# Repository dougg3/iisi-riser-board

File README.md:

# Macintosh IIsi power supply riser board replica

This is a replica of the daughterboard found in the Apple/Sony Macintosh IIsi APS-06 power supply. The part number printed on the original board is AP41S. This PCB often suffers from severe corrosion damage due to electrolytic capacitor leakage, so this project aims to provide you with a way to replace it with a brand new PCB.

To aid with reverse engineering, all of the components were removed from the board and inspected out of circuit. I used pictures of the bare board ([top](barepcb_top.jpg?raw=true), [bottom](barepcb_bottom.jpg?raw=true)) to draw a replica design. The [Bomarc schematics](https://www.macdat.net/files/pdf/apple/schematics/bomarc/mac_iisi.pdf) were a huge help with part identification and understanding the circuit. However, those schematics did have a few mistakes, which I have corrected in my schematics and BOM. My replica design has been successfully used to build a brand new board with all new components except for the two obsolete ICs.

## Schematics

[Here is a link to the schematics in PDF format](iisi-riser-board.pdf?raw=true).

## Build Notes

[Here is an image that shows the names that I arbitrarily gave each component, along with their values](placement.png?raw=true). It may help if you decide to build one yourself.

The trimpot is used to adjust the voltage. If you build one yourself, it may be prudent to test the power supply with a dummy load connected and get the trimpot adjusted properly before trying to use it in an actual Mac IIsi.

## BOM

[Here is the bill of materials in CSV format](iisi-riser-board.csv). All of the parts with the exception of the two obsolete Mitsubishi/Renesas ICs can be purchased brand new from Digi-Key. Note that you need to purchase ten of the leadframe pins for the edge connector.

## Gerbers

[Here is a link to the gerbers](gerbers/) if you want to have boards made yourself. I ordered them as 30.5x36mm, single layer, 0.8 mm thickness, HASL, and solder mask and silkscreen only on one side.

## Purchasing

For convenience, I plan on building some of these up for sale to recoup my costs on this project. I also will save some bare PCBs you can purchase if you just want to move all of your components over from your original corrosion-damaged PCB. Stay tuned for more info on how I will sell these.

## KiCad Design Notes

- The trace widths were very strange on this board, so I just used polygon copper fills to redraw them all. I also manually tweaked each pad's size to bring everything close to the original design.
- The board fails some DRC checks which I have added as exclusions.
- The three GND-to-GND 0-ohm resistors cause three "Unconnected Items" warnings in the DRC. These can be safely ignored.

## Differences from Bomarc reverse-engineered schematics

- The resistor labeled as 8200 ohms in Bomarc's schematic is really 8.2 ohms.
- The chip marked as `44` is really a Mitsubishi/Renesas M51944BML, not a transistor. It's a voltage detector/reset IC.
- The diode marked as `=B` is a Schottky diode; I opted to use the onsemi SB05-05C, which is also marked as `B`.
- I have identified all of the ceramic capacitor values using an LCR meter.
- Pin 9 of the edge connector has been correctly labeled as GND.

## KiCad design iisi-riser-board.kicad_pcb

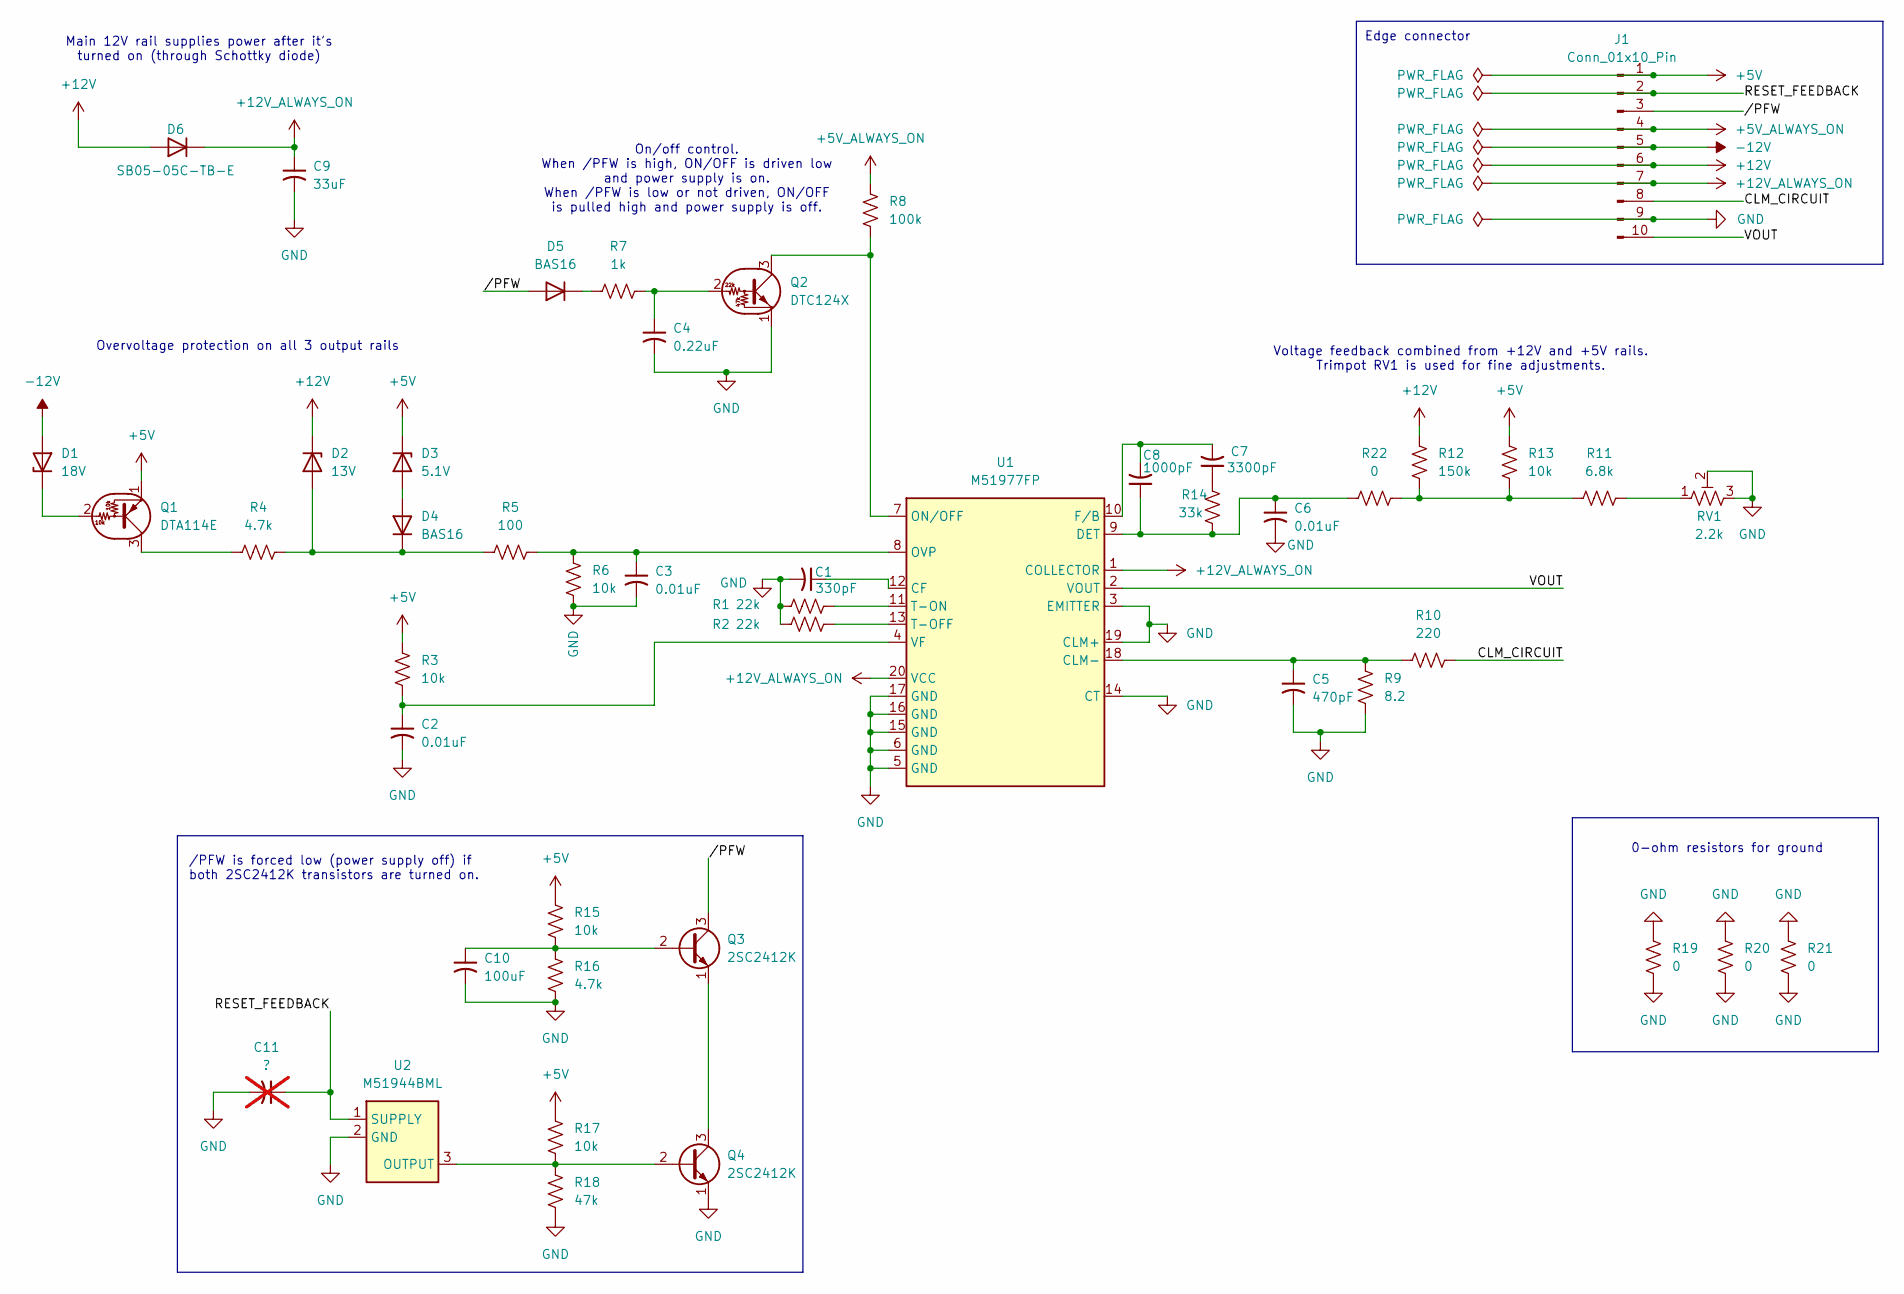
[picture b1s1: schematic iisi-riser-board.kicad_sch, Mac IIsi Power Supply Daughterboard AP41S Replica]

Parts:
C1: 330pF; C_0805_2012Metric; Digi-Key Part 399-C0805C331J5GACTUCT-ND
C2, C3, C6: 0.01uF; C_0805_2012Metric; Digi-Key Part 399-C0805C103K5RACTUCT-ND
C4: 0.22uF; C_1206_3216Metric; Digi-Key Part 445-2283-1-ND
C5: 470pF; C_0805_2012Metric; Digi-Key Part 311-1119-1-ND
C7: 3300pF; C_0805_2012Metric; Digi-Key Part 399-C0805C332J5GACTUCT-ND
C8: 1000pF; C_0805_2012Metric; Digi-Key Part 399-C0805C102J5GACTUCT-ND
C9: 33uF; CP_Elec; Digi-Key Part 565-4768-1-ND
C10: 100uF; CP_Elec; Digi-Key Part 493-3967-1-ND
C11: ?; C_0805_2012Metric; not fitted
D1: 18V; SC-59-Diode; Digi-Key Part MMBZ5248B-FDICT-ND
D2: 13V; SC-59-Diode; Digi-Key Part BZX84C13-FDICT-ND
D3: 5.1V; SC-59-Diode; Digi-Key Part SZBZX84C5V1LT3GOSCT-ND
D4, D5: BAS16; SC-59-Diode; Digi-Key Part 1727-2887-1-ND
D6: SB05-05C-TB-E; SC-59-Diode; Digi-Key Part SB05-05C-TB-EOSCT-ND
J1: Conn_01x10_Pin; EdgeConnector10; Digi-Key Part A122175CT-ND
Q1: DTA114E; SOT-346-Rohm; Digi-Key Part DTA114EKAT146CT-ND
Q2: DTC124X; SOT-346-Rohm; Digi-Key Part DTC124XKAT146CT-ND
Q3, Q4: 2SC2412K; SOT-346-Rohm; Digi-Key Part 2SC2412KT146RCT-ND
R1, R2: 22k; R_0805_2012Metric; Digi-Key Part A129765CT-ND
R3, R6, R13, R15, R17: 10k; R_0805_2012Metric; Digi-Key Part A129761CT-ND
R4, R16: 4.7k; R_0805_2012Metric; Digi-Key Part A129757CT-ND
R5: 100; R_0805_2012Metric; Digi-Key Part P100DACT-ND
R7: 1k; R_0805_2012Metric; Digi-Key Part A129749CT-ND
R8: 100k; R_0805_2012Metric; Digi-Key Part A129773CT-ND
R9: 8.2; R_0805_2012Metric; Digi-Key Part 13-RC0805FR-078R2LCT-ND
R10: 220; R_0805_2012Metric; Digi-Key Part A129741CT-ND
R11: 6.8k; R_0805_2012Metric; Digi-Key Part A127026CT-ND
R12: 150k; R_0805_2012Metric; Digi-Key Part P150KACT-ND
R14: 33k; R_0805_2012Metric; Digi-Key Part P33KDACT-ND
R18: 47k; R_0805_2012Metric; Digi-Key Part 311-47KARCT-ND
R19, R20, R21, R22: 0; R_0805_2012Metric; Digi-Key Part P0.0ACT-ND
RV1: 2.2k; Potentiometer_Bourns_TC33X_Vertical; Digi-Key Part 118-TC33X-1-222ECT-ND
U1: M51977FP; SO-20_5.3x12.6mm_P1.27mm
U2: M51944BML; SOT-89-3

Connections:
+5V: D3.1 (K), J1.1, Q1.1 (E), R3.1, R13.1, R15.1, R17.1
+5V_ALWAYS_ON: J1.4, R8.1
+12V: D2.1 (K), D6.2 (A), J1.6, R12.1
+12V_ALWAYS_ON: C9.1, D6.1 (K), J1.7, U1.1 (COLLECTOR), U1.20 (VCC)
-12V: D1.2 (A), J1.5
/CLM_CIRCUIT: J1.8, R10.1
/RESET_FEEDBACK: C11.1, J1.2, U2.1 (SUPPLY)
/VOUT: J1.10, U1.2 (VOUT)
//PFW: D5.2 (A), J1.3, Q3.3 (C)
GND: C1.2, C2.2, C3.2, C4.2, C5.2, C6.2, C9.2, C10.2, C11.2, J1.9, Q2.1 (E), Q4.1 (E), R1.1, R2.1, R6.1, R9.1, R16.2, R18.2, R19.1, R19.2, R20.1, R20.2, R21.1, R21.2, RV1.2, RV1.3, U1.3 (EMITTER), U1.5 (GND), U1.6 (GND), U1.14 (CT), U1.15 (GND), U1.16 (GND), U1.17 (GND), U1.19 (CLM+), U2.2 (GND)
unnamed: C7.1, R14.2
unnamed: D1.1 (K), Q1.2 (B)
unnamed: D2.2 (A), D4.1 (K), R4.2, R5.1
unnamed: D3.2 (A), D4.2 (A)
unnamed: D5.1 (K), R7.1
unnamed: Q1.3 (C), R4.1
unnamed: C4.1, Q2.2 (B), R7.2
unnamed: Q2.3 (C), R8.2, U1.7 (ON/OFF)
unnamed: C10.1, Q3.2 (B), R15.2, R16.1
unnamed: Q3.1 (E), Q4.3 (C)
unnamed: Q4.2 (B), R17.2, R18.1, U2.3 (OUTPUT)
unnamed: R11.1, RV1.1
unnamed: R11.2, R12.2, R13.2, R22.1
unnamed: C1.1, U1.12 (CF)
unnamed: C5.1, R9.2, R10.2, U1.18 (CLM-)
unnamed: C6.1, C8.1, R14.1, R22.2, U1.9 (DET)
unnamed: C7.2, C8.2, U1.10 (F/B)
unnamed: C3.1, R5.2, R6.2, U1.8 (OVP)
unnamed: R2.2, U1.13 (T-OFF)
unnamed: R1.2, U1.11 (T-ON)
unnamed: C2.1, R3.2, U1.4 (VF)

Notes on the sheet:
0-ohm resistors for ground
On/off control. When /PFW is high, ON/OFF is driven low and power supply is on. When /PFW is low or not driven, ON/OFF is pulled high and power supply is off.
Overvoltage protection on all 3 output rails
Voltage feedback combined from +12V and +5V rails. Trimpot RV1 is used for fine adjustments.
/PFW is forced low (power supply off) if both 2SC2412K transistors are turned on.
Edge connector
Main 12V rail supplies power after it's turned on (through Schottky diode)

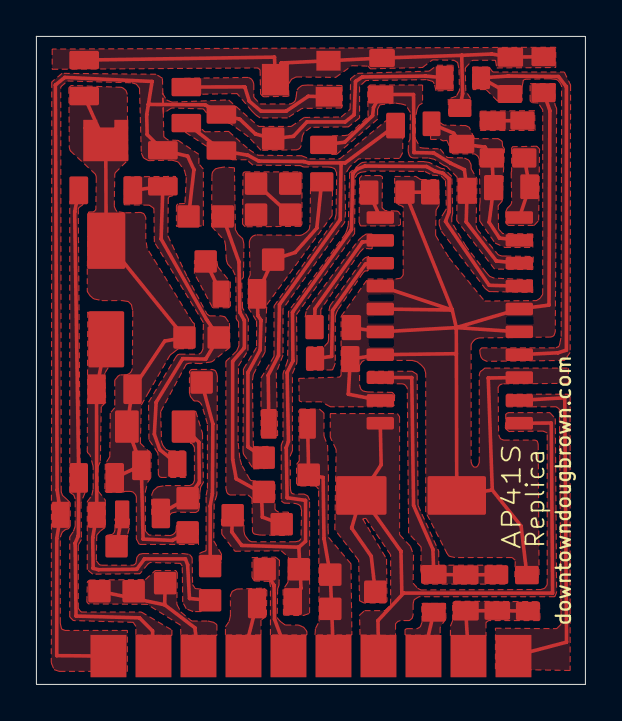
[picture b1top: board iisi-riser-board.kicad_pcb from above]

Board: 2 copper layers, 30.5 x 36.0 mm, 47 parts (0 on the bottom side), 31 nets.

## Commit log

2025-08-27 Add gerbers for replica PCB
2025-08-27 Initial commit of IIsi power supply daughterboard replica design
2025-08-27 Add image showing all components by name and value
2025-08-27 Add Digi-Key part numbers for everything that is brand new
2025-08-27 Add BOM
2025-08-27 Add picture of assembled board
2025-08-27 Add schematic PDF
2025-08-27 Add README
2025-09-01 Add big capacitors to paste layer
    I left them out initially because I was using hot air and manually
    soldering those two caps on afterward. With reflow, there's no reason to
    leave the caps out from the solder paste.
